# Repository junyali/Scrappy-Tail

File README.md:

# Scrappy Tail

A DIY USB 2.0 Hub with 4 Type-A ports and a Type-C input, with a cute 3D printed scrappy cat case!! :3

Scrappy Tail connects to your device using USB Type-C (hence the cable making it look like a tail!) and gives you 4 additional USB Type-A ports. It uses the SL2.1A hub controller, so it uses USB 2.0 interface and thus speeds are limited to 480Mbps

PCB designed in KiCAD and CAD designed in OnShape. 

# Preview

| Description         | Image                            |
|---------------------|----------------------------------|
| Schematic           |       |
| PCB                 |             |
| 3D PCB Render Front |    |
| 3D PCB Render Back  |     |
| CAD + PCB           |  |

# BOM

This one's a bit of an expensive one thanks to the PCBA fees.

See the original BOM under `bom.csv`

## PCB Prototype + individual components only

| Component                                                         | Quantity | LCSC Part #     | Price (USD) | LCSC Link                                                                                                                        |
|-------------------------------------------------------------------|----------|-----------------|-------------|----------------------------------------------------------------------------------------------------------------------------------|
| 100uF Ceramic Capacitor                                           | 7        | CL31A107MQHNNNE | 0.34        | https://lcsc.com/product-detail/Multilayer-Ceramic-Capacitors-MLCC-SMD-SMT_Samsung-Electro-Mechanics-CL31A107MQHNNNE_C15008.html |
| Schottky Diode 1206                                               | 1        | C466498         | 0.47        | https://lcsc.com/product-detail/Schottky-Diodes_High-Diode-SS14_C466498.html                                                     |
| USB C Receptacle JAE DX07S016JA1R1500                             | 1        | C3197885        | 0.97        | https://lcsc.com/product-detail/USB-Connectors_JAE-DX07S016JA1R1500_C3197885.html                                                |
| USB A Receptacle Molex 67643 Horizontal                           | 4        | C2765194        | 0.88        | https://lcsc.com/product-detail/USB-Connectors_MOLEX-67643-3911_C2765194.html                                                    |
| 5.1kΩ Resistor 0603                                               | 2        | C105580         | 0.12        | https://lcsc.com/product-detail/Chip-Resistor-Surface-Mount_YAGEO-RC0603FR-075K1L_C105580.html                                   |
| CoreChips SL2.1A                                                  | 1        | C192893         | 1.31        | https://lcsc.com/product-detail/USB-HUB-Controllers_CoreChips-SL2-1A_C192893.html                                                |
| PCB manufactured by JLCPCB (incl shipping, taxes, customs)        | 5        | N/A             | 3.10        | https://jlcpcb.com                                                                                                               |
| Economic PCBA assembled by JLCPCB (incl shipping, taxes, customs) | 2        | N/A             | 52.38       | https://jlcpcb.com                                                                                                               |

Subtotal (excluding PCBA): `US$7.19`

Estimated cost (PCBA which includes parts and PCB): `US$55.48`

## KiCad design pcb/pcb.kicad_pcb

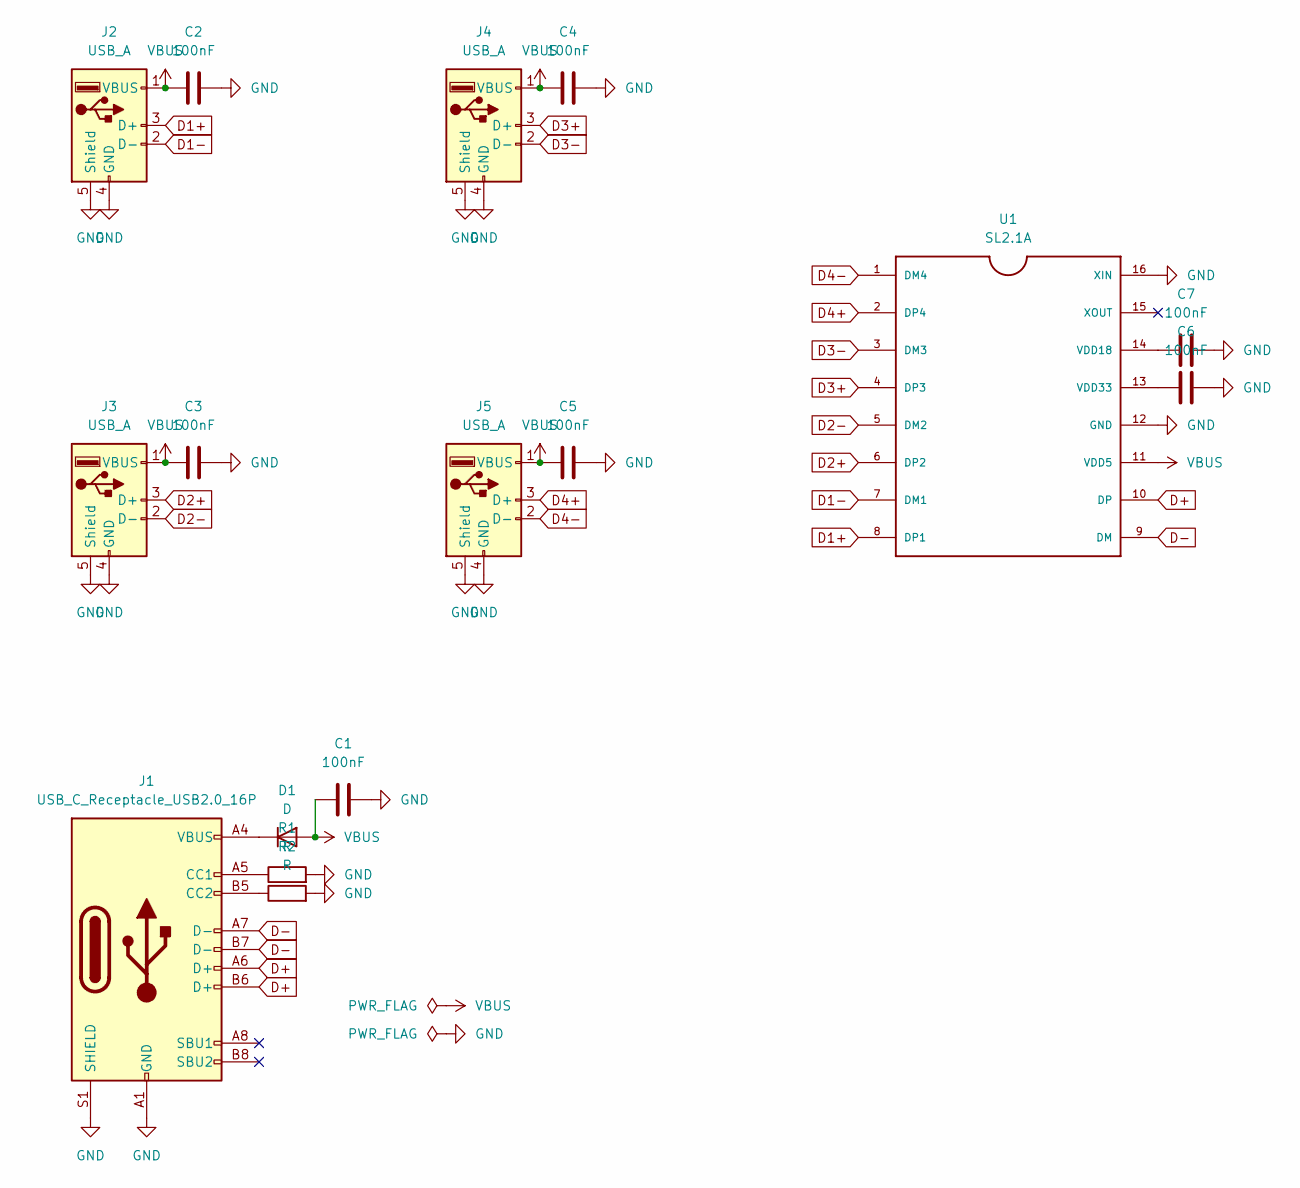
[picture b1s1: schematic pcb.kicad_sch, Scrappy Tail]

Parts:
C1, C2, C3, C4, C5, C6, C7: 100nF; C_1206_3216Metric; MPN CL31A107MQHNNNE
D1: D; D_1206_3216Metric; MPN C466498
J1: USB_C_Receptacle_USB2.0_16P; USB_C_Receptacle_JAE_DX07S016JA1R1500_3D; MPN C3197885
J2, J3, J4, J5: USB_A; USB_A_Molex_67643_Horizontal; MPN C2765194
R1, R2: R; R_0603_1608Metric; MPN C105580
U1: SL2.1A; SO16; MPN C192893

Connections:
D1+: J2.3 (D+), U1.8 (DP1)
D1-: J2.2 (D-), U1.7 (DM1)
D2+: J3.3 (D+), U1.6 (DP2)
D2-: J3.2 (D-), U1.5 (DM2)
D3+: J4.3 (D+), U1.4 (DP3)
D3-: J4.2 (D-), U1.3 (DM3)
D4+: J5.3 (D+), U1.2 (DP4)
D4-: J5.2 (D-), U1.1 (DM4)
D+: J1.A6 (D+), J1.B6 (D+), U1.10 (DP)
D-: J1.A7 (D-), J1.B7 (D-), U1.9 (DM)
GND: C1.2, C2.2, C3.2, C4.2, C5.2, C6.2, C7.2, J1.A1 (GND), J1.A12 (GND), J1.B1 (GND), J1.B12 (GND), J1.S1 (SHIELD), J2.4 (GND), J2.5 (Shield), J3.4 (GND), J3.5 (Shield), J4.4 (GND), J4.5 (Shield), J5.4 (GND), J5.5 (Shield), R1.2, R2.2, U1.12 (GND), U1.16 (XIN)
unnamed: D1.1 (K), J1.A4 (VBUS), J1.A9 (VBUS), J1.B4 (VBUS), J1.B9 (VBUS)
unnamed: J1.A5 (CC1), R1.1
unnamed: J1.B5 (CC2), R2.1
unnamed: C7.1, U1.14 (VDD18)
unnamed: C6.1, U1.13 (VDD33)
VBUS: C1.1, C2.1, C3.1, C4.1, C5.1, D1.2 (A), J2.1 (VBUS), J3.1 (VBUS), J4.1 (VBUS), J5.1 (VBUS), U1.11 (VDD5)

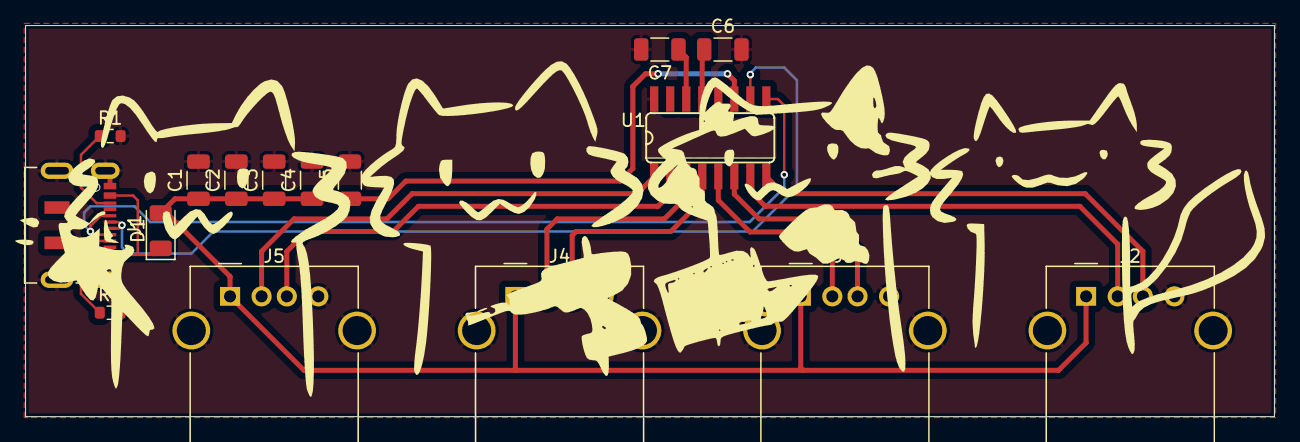
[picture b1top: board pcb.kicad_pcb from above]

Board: 2 copper layers, 99.0 x 31.0 mm, 16 parts (0 on the bottom side), 17 nets.

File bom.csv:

Designator,Footprint,Quantity,Value,LCSC Part #, Price, LCSC Link
"C1, C2, C3, C4, C5, C6, C7",1206,7,100nF,CL31A107MQHNNNE,0.34,https://lcsc.com/product-detail/Multilayer-Ceramic-Capacitor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
D1,1206,1,D,C466498,0.47,https://lcsc.com/product-detail/Schottky-Diodes_High-Diode-S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
J1,USB_C_Receptacle_JAE_DX07S016JA1R1500_3D,1,USB_C_Receptacle_USB2.0_16P,C3197885,0.97,https://lcsc.com/product-detail/USB-Connectors_JAE-DX07S016J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
"J2, J3, J4, J5",USB_A_Molex_67643_Horizontal,4,USB_A,C2765194,0.88,https://lcsc.com/product-detail/USB-Connectors_JAE-DX07S016J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
"R1, R2",0603,2,R,C105580,0.12,https://lcsc.com/product-detail/Chip-Resistor-Surface-Mount_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
U1,SO16,1,SL2.1A,C192893,1.31,https://lcsc.com/product-detail/USB-HUB-Controllers_CoreChip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

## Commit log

2025-07-05 Add JOURNAL.md
2025-07-18 Add PCB
2025-07-18 Update PCB
2025-07-18 Add CAD files
2025-07-18 Add production files
2025-07-18 Add README.md
2025-07-18 Add bom.csv (thank .gitignore)
2025-07-18 Add bom.csv (thanks .gitignore)
2025-07-18 Fix incorrect links
2025-07-18 Add PaP files
